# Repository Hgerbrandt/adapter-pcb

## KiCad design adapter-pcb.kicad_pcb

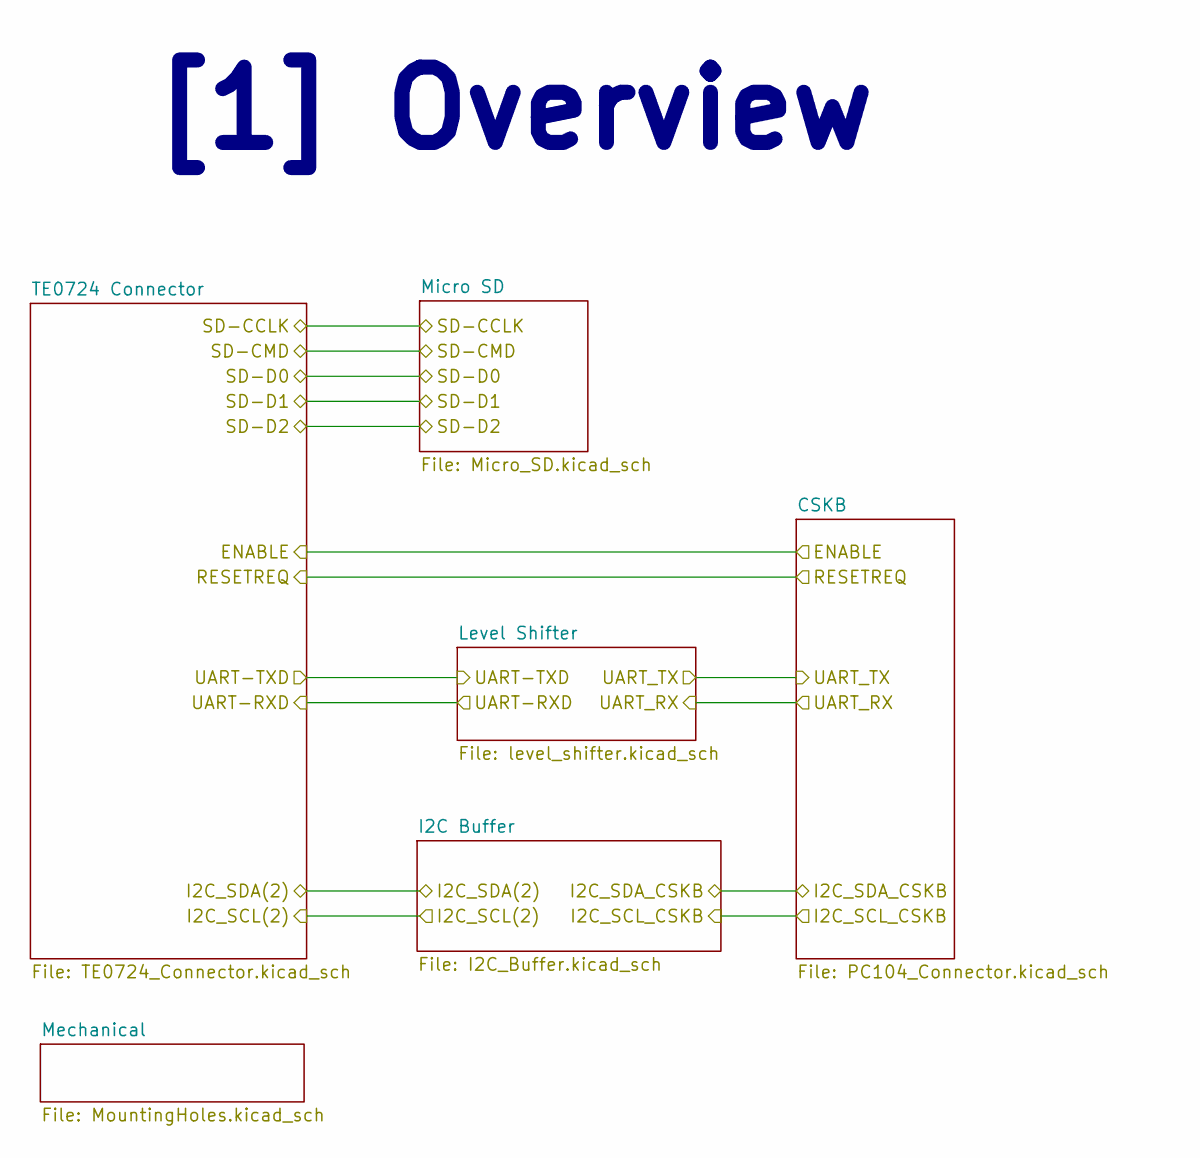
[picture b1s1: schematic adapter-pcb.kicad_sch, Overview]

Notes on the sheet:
[1] Overview

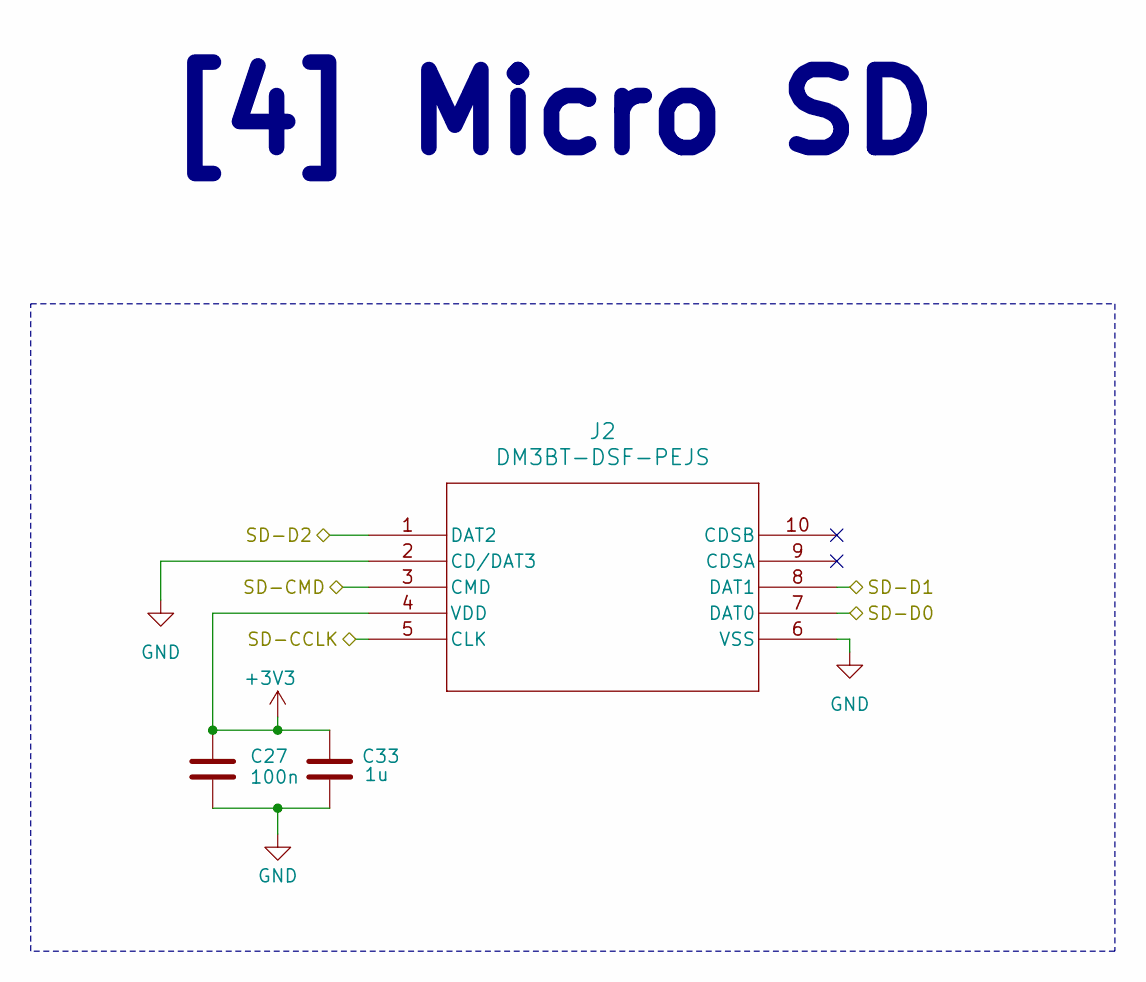
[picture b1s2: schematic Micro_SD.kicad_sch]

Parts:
C27: 100n; C_0603_1608Metric; MANUFACTURER_PART_NUMBER GCM155R71H104KE02D
C33: 1u; C_0805_2012Metric; MANUFACTURER_PART_NUMBER GRT155R61A105KE01D
J2: DM3BT-DSF-PEJS; DM3BT_DSF_PEJS; MANUFACTURER_PART_NUMBER DM3BT-DSF-PEJS

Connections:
+3V3: C27.1, C33.1, J2.4 (VDD); also elsewhere on the board
GND: C27.2, C33.2, J2.2 (CD/DAT3), J2.6 (VSS); also elsewhere on the board
SD-CCLK: J2.5 (CLK); also elsewhere on the board
SD-CMD: J2.3 (CMD); also elsewhere on the board
SD-D0: J2.7 (DAT0); also elsewhere on the board
SD-D1: J2.8 (DAT1); also elsewhere on the board
SD-D2: J2.1 (DAT2); also elsewhere on the board

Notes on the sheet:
[4] Micro SD

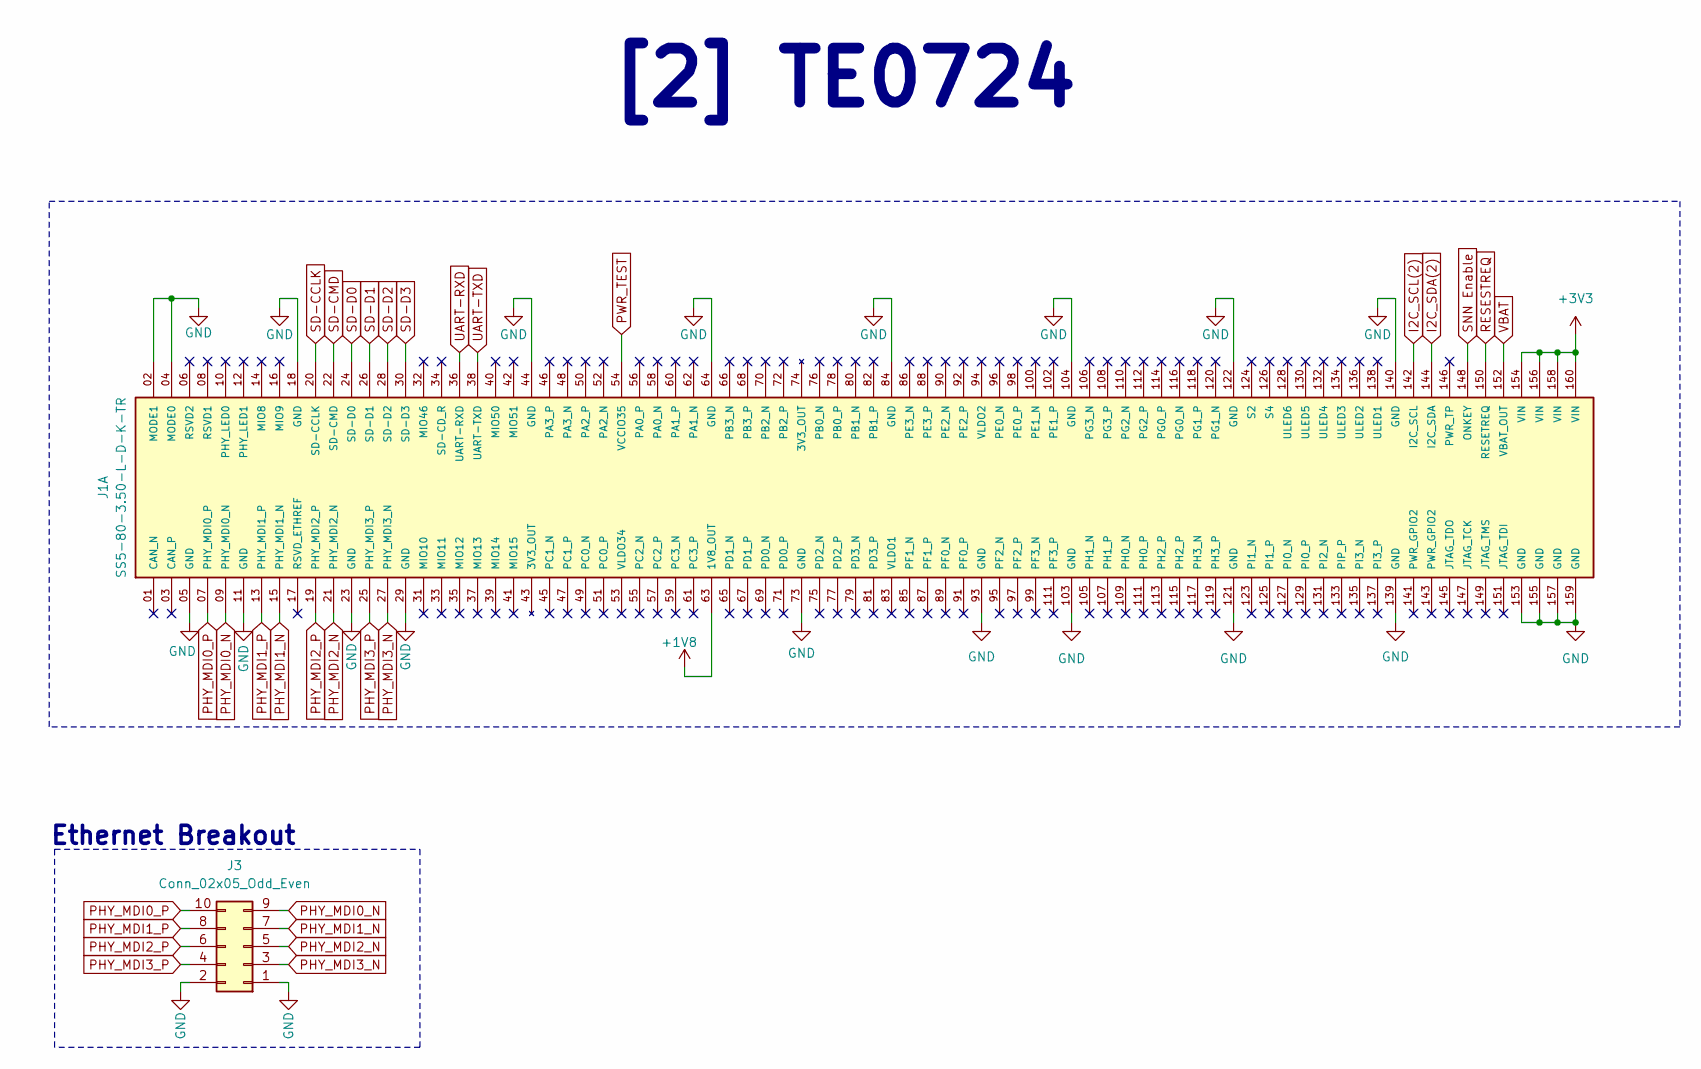
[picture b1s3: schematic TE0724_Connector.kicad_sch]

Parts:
J1: SS5-80-3.50-L-D-K-TR; SAMTEC_SS5-80-3.50-X-D-K-XX; PARTREV F
J3: Conn_02x05_Odd_Even; PinSocket_2x05_P2.54mm_Vertical

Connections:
+1V8: J1.63 (1V8_OUT); also elsewhere on the board
+3V3: J1.154 (VIN), J1.156 (VIN), J1.158 (VIN), J1.160 (VIN); also elsewhere on the board
GND: J1.02 (MODE1), J1.04 (MODE0), J1.05 (GND), J1.11 (GND), J1.18 (GND), J1.23 (GND), J1.29 (GND), J1.44 (GND), J1.64 (GND), J1.73 (GND), J1.84 (GND), J1.93 (GND), J1.103 (GND), J1.104 (GND), J1.121 (GND), J1.122 (GND), J1.139 (GND), J1.140 (GND), J1.153 (GND), J1.155 (GND), J1.157 (GND), J1.159 (GND), J3.1, J3.2; also elsewhere on the board
I2C_SCL(2): J1.142 (I2C_SCL); also elsewhere on the board
I2C_SDA(2): J1.144 (I2C_SDA); also elsewhere on the board
PHY_MDI0_N: J1.09 (PHY_MDI0_N), J3.9
PHY_MDI0_P: J1.07 (PHY_MDI0_P), J3.10
PHY_MDI1_N: J1.15 (PHY_MDI1_N), J3.7
PHY_MDI1_P: J1.13 (PHY_MDI1_P), J3.8
PHY_MDI2_N: J1.21 (PHY_MDI2_N), J3.5
PHY_MDI2_P: J1.19 (PHY_MDI2_P), J3.6
PHY_MDI3_N: J1.27 (PHY_MDI3_N), J3.3
PHY_MDI3_P: J1.25 (PHY_MDI3_P), J3.4
PWR_TEST: J1.54 (VCCIO35)
RESESTREQ: J1.150 (RESETREQ); also elsewhere on the board
SD-CCLK: J1.20 (SD-CCLK); also elsewhere on the board
SD-CMD: J1.22 (SD-CMD); also elsewhere on the board
SD-D0: J1.24 (SD-D0); also elsewhere on the board
SD-D1: J1.26 (SD-D1); also elsewhere on the board
SD-D2: J1.28 (SD-D2); also elsewhere on the board
SD-D3: J1.30 (SD-D3)
SNN Enable: J1.148 (ONKEY); also elsewhere on the board
UART-RXD: J1.36 (UART-RXD); also elsewhere on the board
UART-TXD: J1.38 (UART-TXD); also elsewhere on the board
VBAT: J1.152 (VBAT_OUT)

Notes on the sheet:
[2] TE0724
Ethernet Breakout

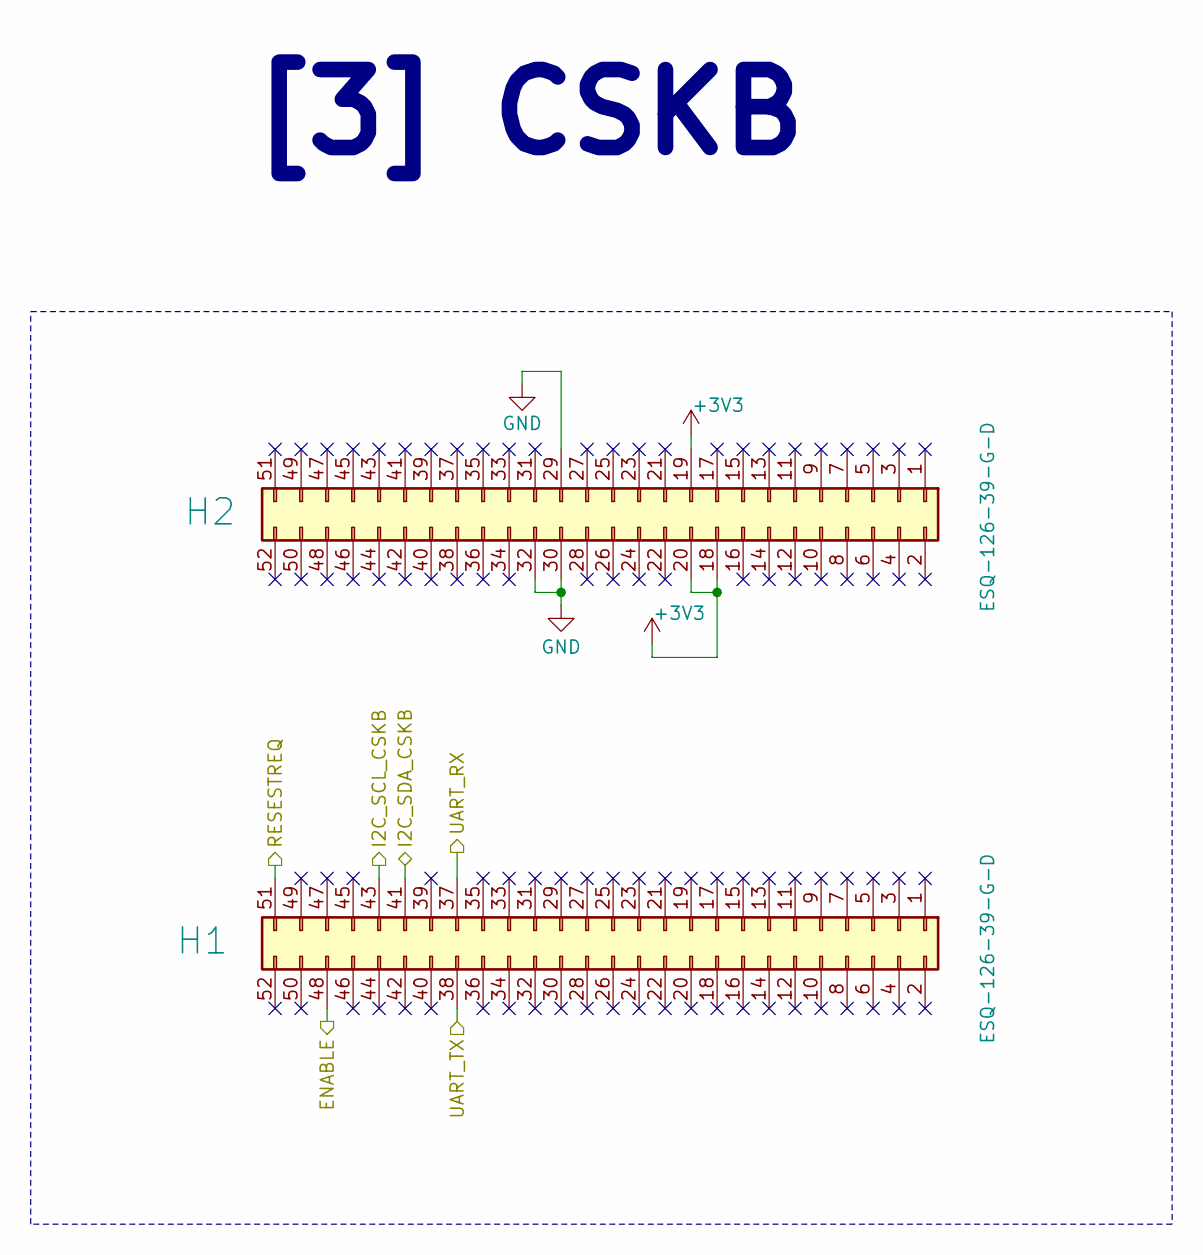
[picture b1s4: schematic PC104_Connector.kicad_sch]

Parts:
H1, H2: ESQ-126-39-G-D; RHDR52W64P254_2X26_6654X495X1135P; MANUFACTURER_PART_NUMBER ESQ-126-39-G-D

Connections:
+3V3: H2.18, H2.19, H2.20; also elsewhere on the board
GND: H2.29, H2.30, H2.32; also elsewhere on the board
I2C_SCL_CSKB: H1.43; also elsewhere on the board
I2C_SDA_CSKB: H1.41; also elsewhere on the board
RESESTREQ: H1.51; also elsewhere on the board
SNN Enable: H1.48; also elsewhere on the board
UART_RX: H1.37; also elsewhere on the board
UART_TX: H1.38; also elsewhere on the board

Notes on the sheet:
[3] CSKB

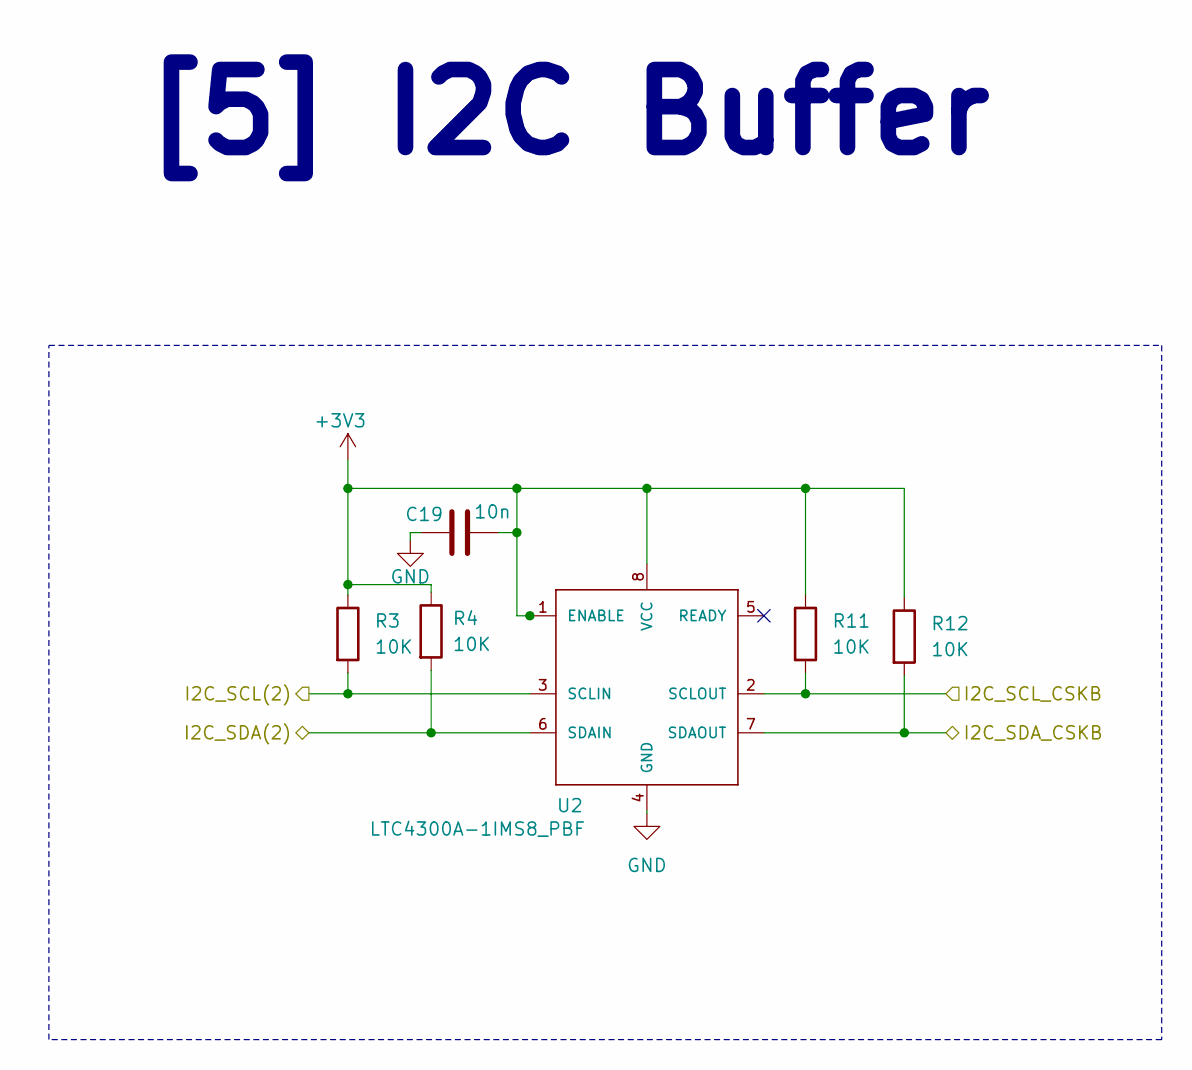
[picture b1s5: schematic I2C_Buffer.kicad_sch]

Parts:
C19: 10n; C_0402_1005Metric; MANUFACTURER_PART_NUMBER GCM155R71H103KA55J
R3, R4, R11, R12: 10K; R_0402_1005Metric; MANUFACTURER_PART_NUMBER MCS0402MD1002BE100
U2: LTC4300A-1IMS8_PBF; MANUFACTURER_PART_NUMBER ltc4300a1ims8

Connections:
+3V3: C19.2, R3.1, R4.1, R11.1, R12.1, U2.1 (ENABLE), U2.8 (VCC); also elsewhere on the board
GND: C19.1, U2.4 (GND); also elsewhere on the board
I2C_SCL(2): R3.2, U2.3 (SCLIN); also elsewhere on the board
I2C_SCL_CSKB: R11.2, U2.2 (SCLOUT); also elsewhere on the board
I2C_SDA(2): R4.2, U2.6 (SDAIN); also elsewhere on the board
I2C_SDA_CSKB: R12.2, U2.7 (SDAOUT); also elsewhere on the board

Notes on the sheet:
[5] I2C Buffer

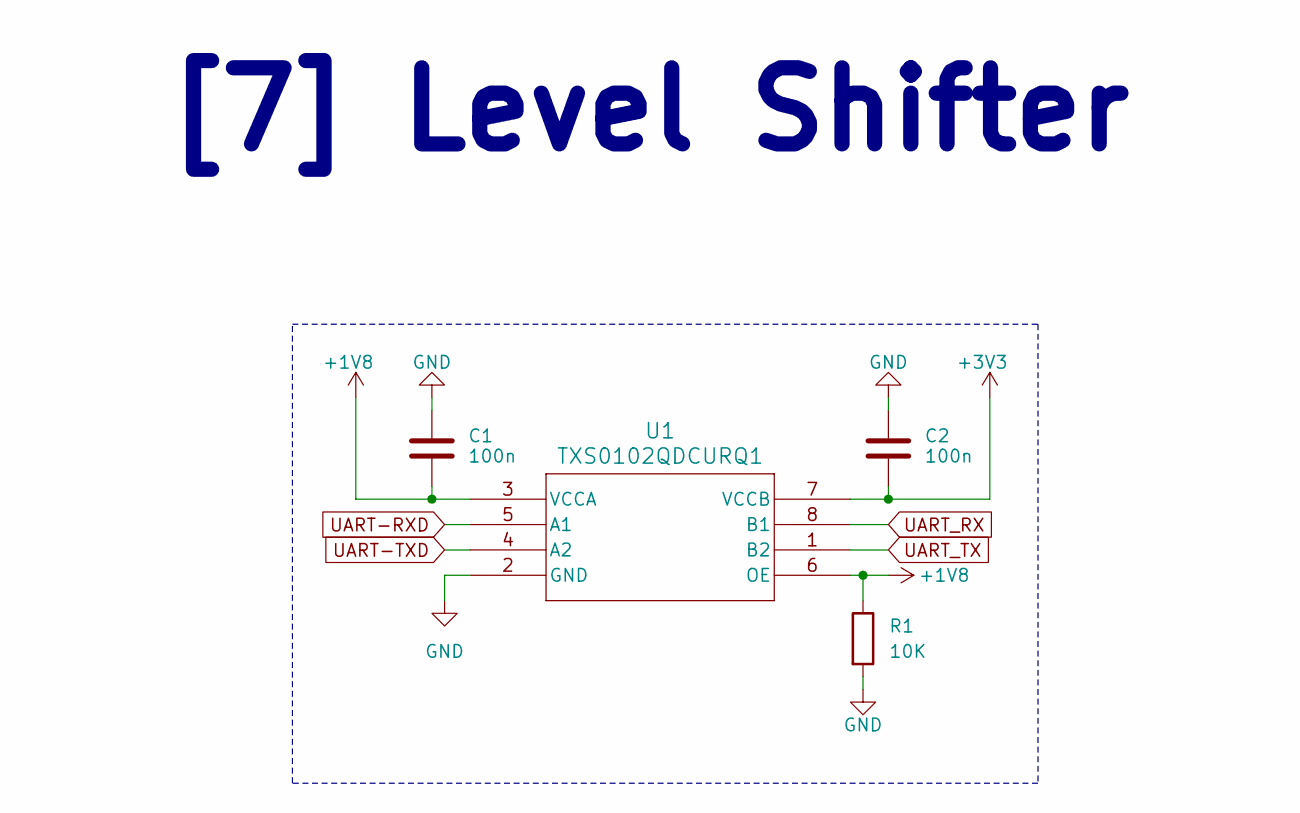
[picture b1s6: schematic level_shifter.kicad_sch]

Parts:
C1, C2: 100n; C_0603_1608Metric; MANUFACTURER_PART_NUMBER GCM155R71H104KE02D
R1: 10K; R_0402_1005Metric
U1: TXS0102QDCURQ1; MANUFACTURER_PART_NUMBER TXS0102QDCURQ1

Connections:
+1V8: C1.2, R1.1, U1.3 (VCCA), U1.6 (OE); also elsewhere on the board
+3V3: C2.2, U1.7 (VCCB); also elsewhere on the board
GND: C1.1, C2.1, R1.2, U1.2 (GND); also elsewhere on the board
UART-RXD: U1.5 (A1); also elsewhere on the board
UART-TXD: U1.4 (A2); also elsewhere on the board
UART_RX: U1.8 (B1); also elsewhere on the board
UART_TX: U1.1 (B2); also elsewhere on the board

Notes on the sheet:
[7] Level Shifter

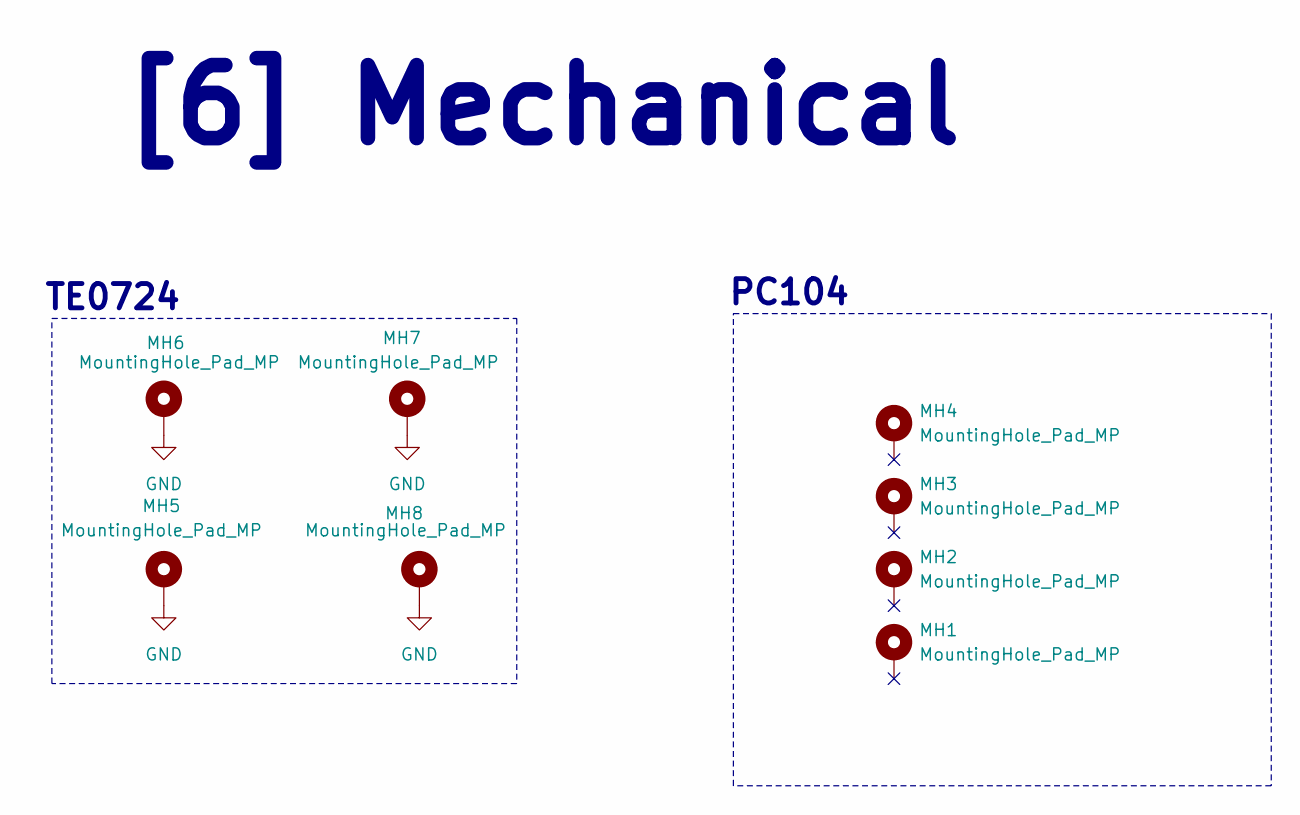
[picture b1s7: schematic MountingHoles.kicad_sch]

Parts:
MH1, MH2, MH3, MH4: MountingHole_Pad_MP; MountingHole_3.18mm_6.35mm_Pad
MH5, MH6, MH7, MH8: MountingHole_Pad_MP; MountingHole_2.2mm_M2_Pad

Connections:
GND: MH5.1, MH6.1, MH7.1, MH8.1; also elsewhere on the board

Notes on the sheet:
PC104
[6] Mechanical
TE0724

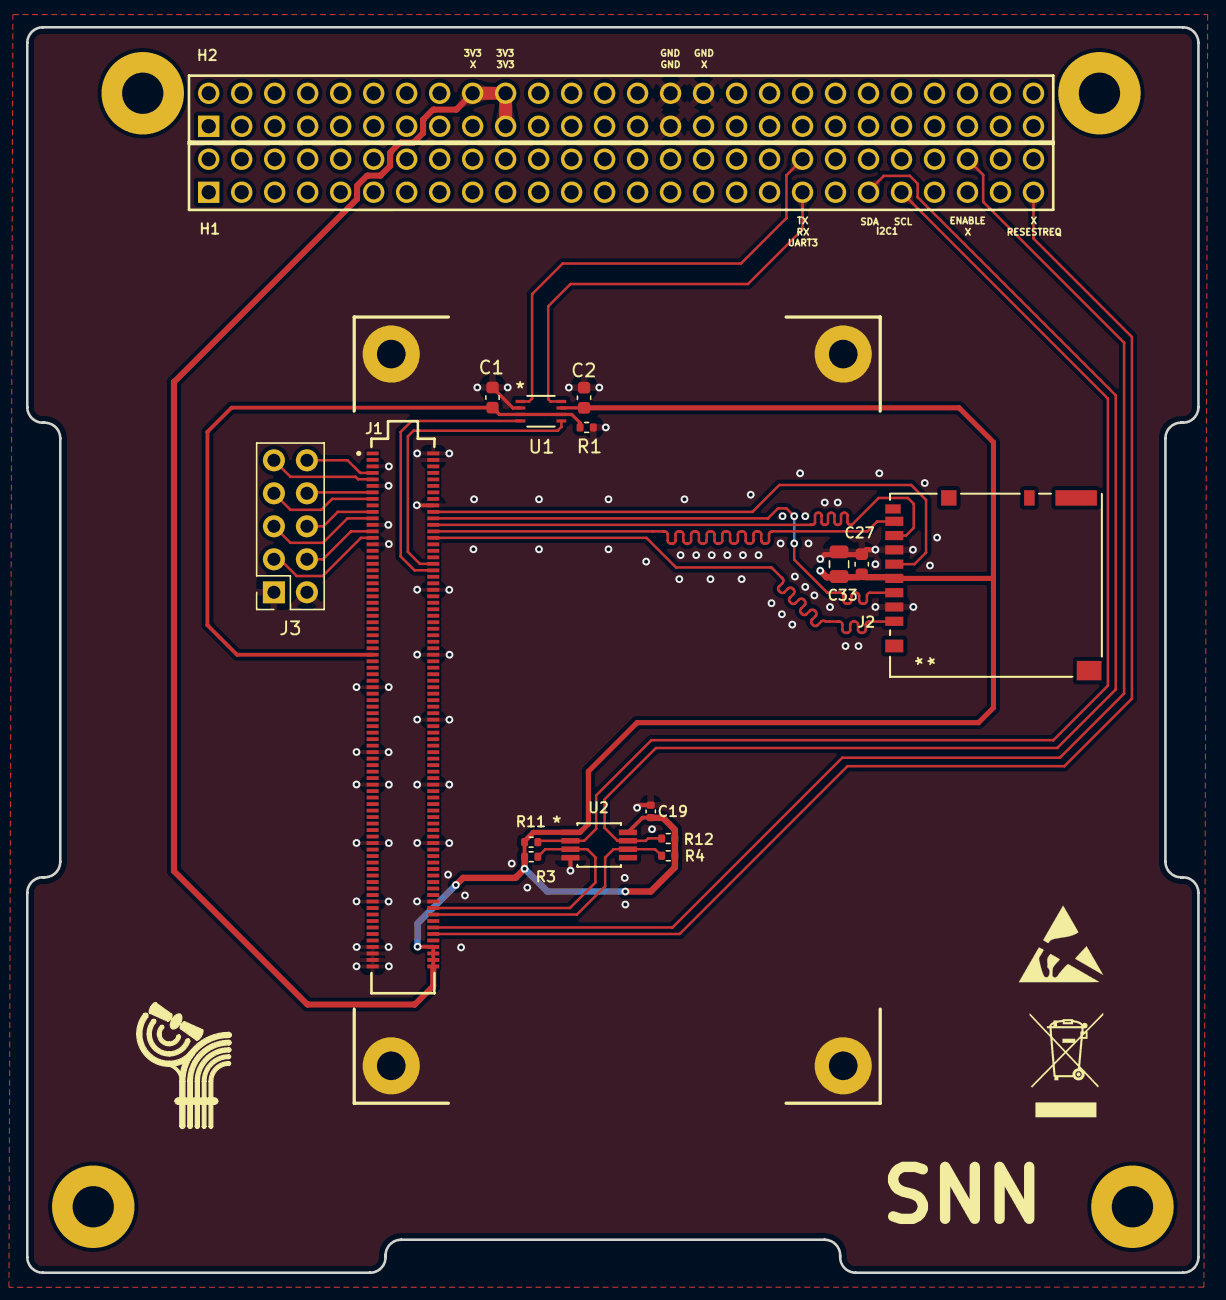
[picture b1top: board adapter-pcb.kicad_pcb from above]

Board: 2 copper layers, 90.2 x 95.9 mm, 25 parts (0 on the bottom side), 26 nets.

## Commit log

2026-02-22 BOM update
    completed the BOM list
2026-02-22 Moved SD Card Slot
2026-02-24 Made some minor adjustments
2026-02-28 fixed 3D models
2026-03-07 Removed SPI Connections
2026-03-08 Added hierarchical lables to the schematic
2026-03-16 Added level shifter and breakout for ethernet
